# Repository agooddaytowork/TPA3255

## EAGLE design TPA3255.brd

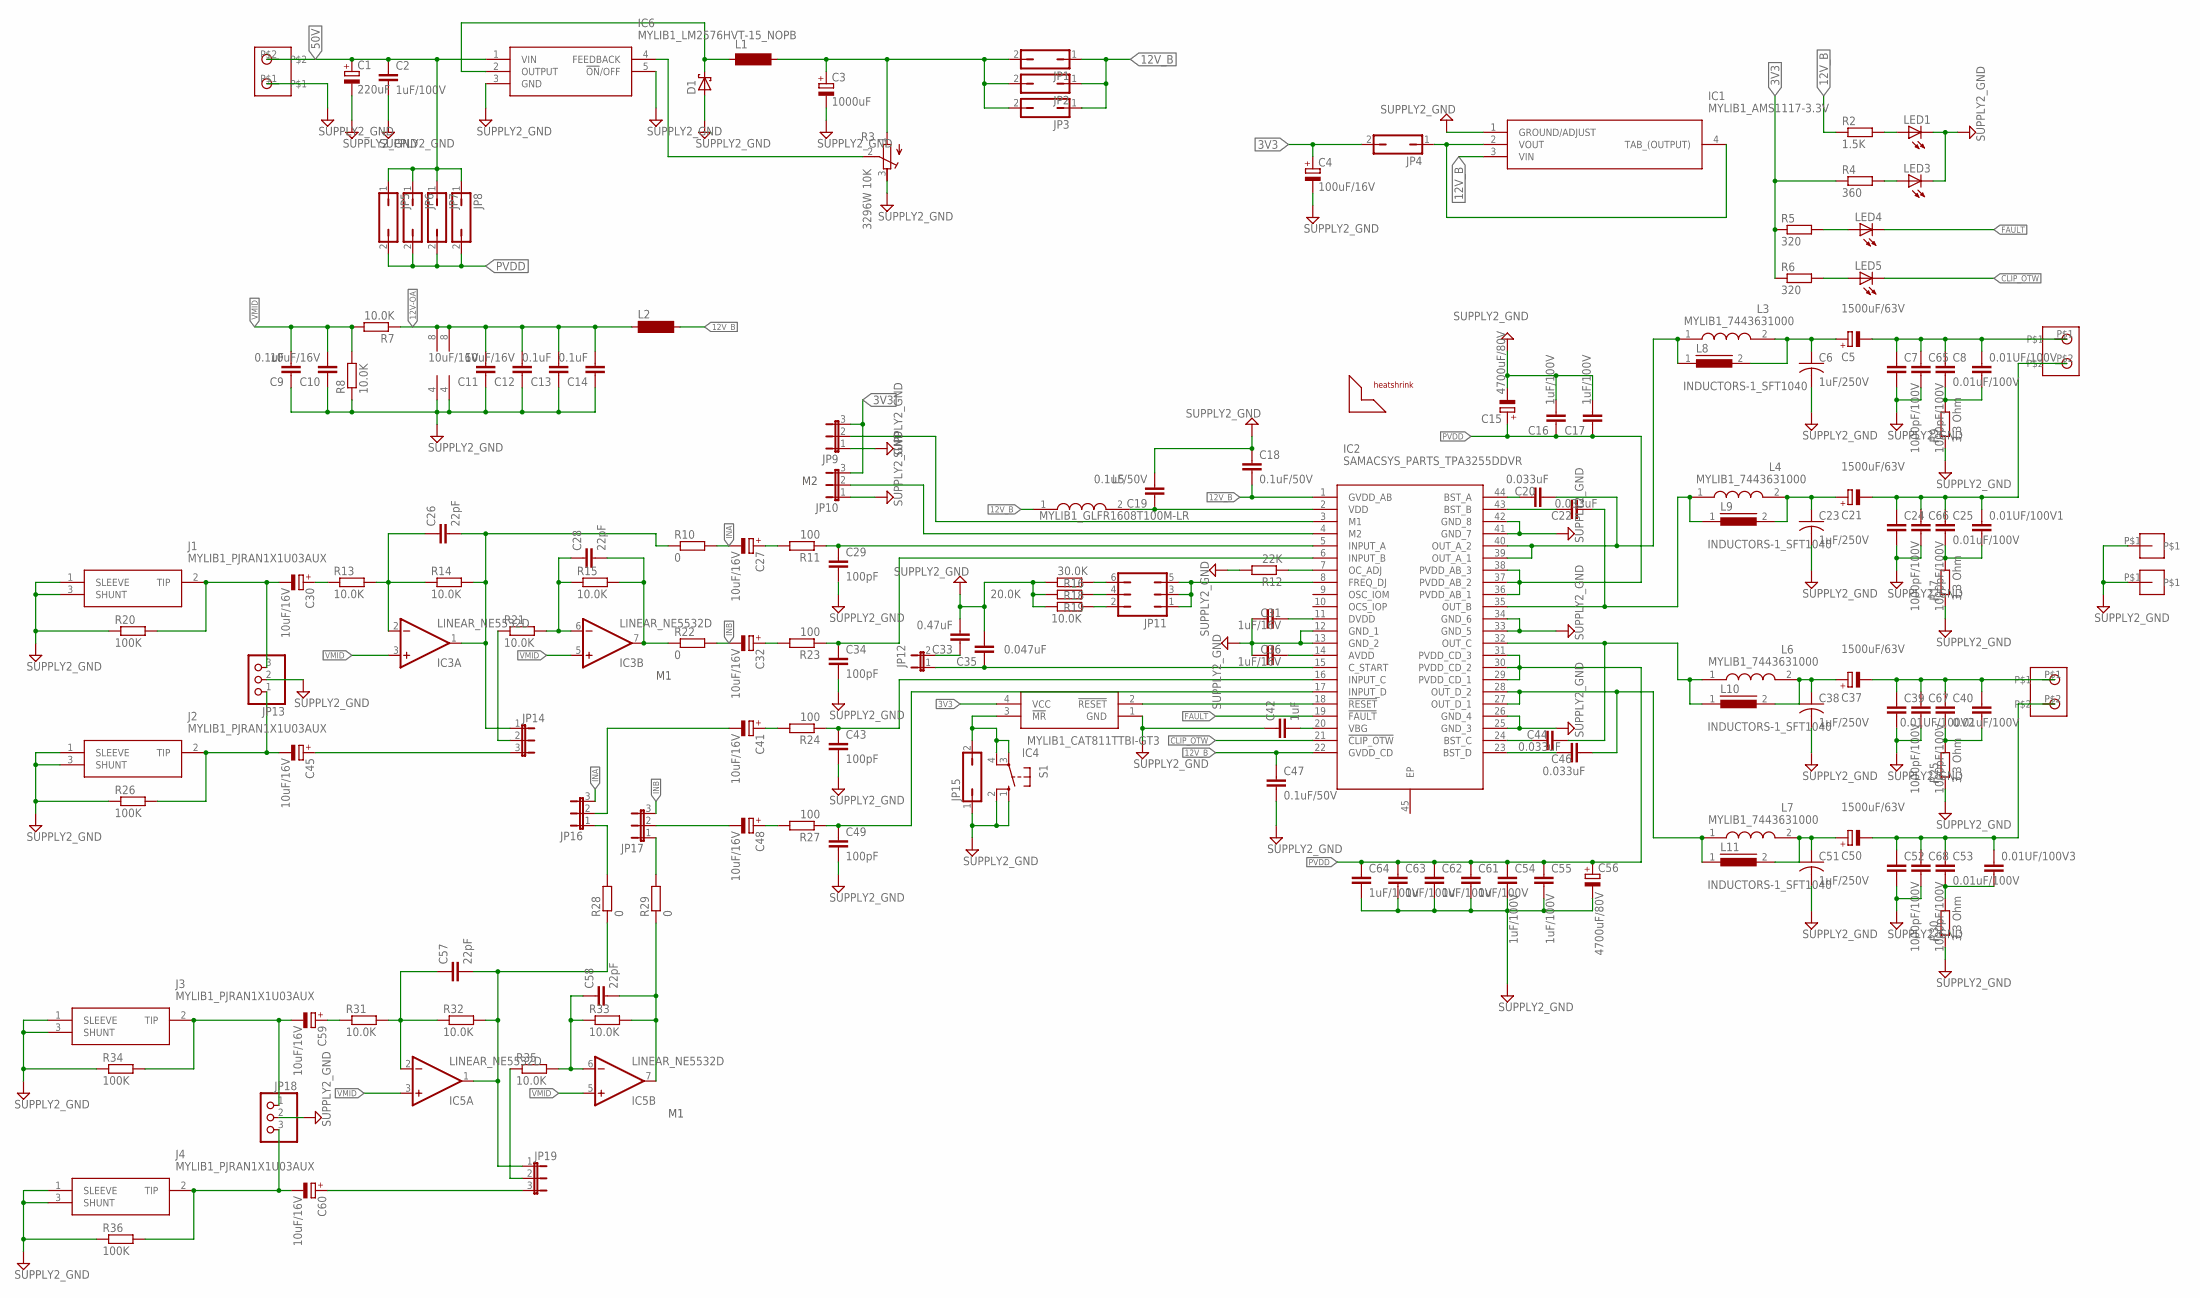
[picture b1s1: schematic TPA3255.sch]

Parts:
0.01UF/100V, 0.01UF/100V1, 0.01UF/100V2, 0.01UF/100V3: RCL_C-EU102-054X133; RCL_C102-054X133
C1: 220uF; RCL_E7,5-18
C2, C16, C17, C54, C55: 1uF/100V; RCL_C150-054X183
C3: 1000uF; RCL_E5-10,5
C4: 100uF/16V; RESISTOR_PANASONIC_B:1
C5, C21, C37, C50: 1500uF/63V; RCL_EB22,5D
C6, C23, C38, C51: 1uF/250V; RCL_C225-108X268
C7, C24, C39, C52: 1000pF/100V; RCL_C1206
C8, C25, C40, C53: 0.01uF/100V; RCL_C0603
C9, C13, C14: 0.1uF; RCL_C0805
C10, C11, C12: 10uF/16V; RCL_C0805
C15, C56: 4700uF/80V; RCL_EB35D
C18, C19, C47: 0.1uF/50V; RCL_C0603
C20, C22, C44, C46: 0.033uF; RCL_C0603K
C26, C28, C57, C58: 22pF; RCL_C0805
C27, C30, C32, C41, C45, C48, C59, C60: 10uF/16V; RCL_PANASONIC_B
C29, C34, C43, C49: 100pF; RCL_C0805
C31, C36: 1uF/16V; RCL_C0603
C33: 0.47uF; RCL_C0603
C35: 0.047uF; RCL_C0805
C42: 1uF; RESISTOR_C0603:1
C61, C62, C63, C64: 1uF/100V; RCL_C1206
C65, C66, C67, C68: 1000pF/100V; RCL_C050-025X075
D1: DIODE_SCHOTTKY-DIODESMD; DIODE_SMB
H1: 28x28mm; MYLIB1_HEATSHRINK-28X28MM
IC1: MYLIB1_AMS1117-3.3V; MYLIB1_SOT229P700X180-4N
IC2: SAMACSYS_PARTS_TPA3255DDVR; SAMACSYS_PARTS_SOP64P810X120-45N
IC3, IC5: LINEAR_NE5532D; LINEAR_SO08
IC4: MYLIB1_CAT811TTBI-GT3; MYLIB1_4-PIN-SOT-143(BI-SUFFIX-CASE-5
IC6: MYLIB1_LM2576HVT-15_NOPB; MYLIB1_LM2576HVT15NOPB
J1, J2, J3, J4: MYLIB1_PJRAN1X1U03AUX
JP1, JP2, JP3, JP4, JP5, JP6, JP7, JP8, JP15: JUMPER_JP1Q; JUMPER_JP1
JP9, JP10, JP14, JP16, JP17, JP19: JUMPER_JP2E; JUMPER_JP2
JP11: JUMPER_JP3Q
JP12: JUMPER_JP1E; JUMPER_JP1
JP13, JP18: PINHEAD_PINHD-1X3; PINHEAD_1X03
L1, L2: INDUCTOR-NEOSID_BS11
L3, L4, L6, L7: MYLIB1_7443631000; MYLIB1_WE-HCF_201322
L5: MYLIB1_GLFR1608T100M-LR; MYLIB1_INDC1608X100N
L8, L9, L10, L11: INDUCTORS-1_SFT1040
LED1, LED3, LED4, LED5: LED_LEDCHIP-LED0805; LED_CHIP-LED0805
R2: 1.5K; RCL_M0805
R3: 3296W 10K; RCL_RTRIM3296W
R4: 360; RCL_M0805
R5, R6: 320; RCL_M0805
R7, R8, R13, R14, R15, R21, R31, R32, R33, R35: 10.0K; RESISTOR_M0805:1
R9, R17, R25, R30: 3.3 Ohm; RESISTOR_R0805:1
R10, R22, R28, R29: 0; RESISTOR_M0805:1
R11, R23, R24, R27: 100; RCL_M0805
R12: 22K; RCL_M0805
R16: 30.0K; RCL_R0805
R18: 20.0K; RESISTOR_R0603:1
R19: 10.0K; RCL_R0805
R20, R26, R34, R36: 100K; RESISTOR_M0805:1
S1: SWITCH-OMRON_10-XX; SWITCH-OMRON_B3F-10XX
T1, T2, T4: MYLIB1_5MM-2PIN-TERMINAL; MYLIB1_3MM-2PIN-TERMINAL
U$1, U$2: MYLIB1_5MM-1PIN-TERMINAL

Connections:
3V3: C4.+, IC4.4 (VCC), JP4.2, JP9.3, JP10.3, R4.1, R5.1, R6.1
12V: C3.+, JP1.2, JP2.2, JP3.2, L1.2, R3.1 (A)
12V-OA: C11.2, C12.2, C13.2, C14.2, IC3.8 (V+), IC5.8 (V+), L2.1, R7.1
12V_B: C18.2, C47.1, IC1.3 (VIN), IC2.1 (GVDD_AB), IC2.22 (GVDD_CD), JP1.1, JP2.1, JP3.1, L2.2, L5.1, R2.1
50V: C1.+, C2.1, IC6.1 (VIN), JP5.1, JP6.1, JP7.1, JP8.1, T1.P$2
CLIP_OTW: IC2.21 (!CLIP_OTW), LED5.C
FAULT: IC2.19 (!FAULT), LED4.C
GND: C1.-, C2.2, C3.-, C4.-, C6.2, C7.2, C9.1, C10.1, C11.1, C12.1, C13.1, C14.1, C15.-, C16.2, C17.2, C18.1, C19.2, C23.2, C24.2, C29.2, C31.1, C33.2, C34.2, C35.2, C36.1, C38.2, C39.2, C42.1, C43.2, C47.2, C49.2, C51.2, C52.2, C54.2, C55.2, C56.-, C61.2, C62.2, C63.2, C64.2, C65.2, C66.2, C67.2, C68.2, D1.A, IC1.1 (GROUND/ADJUST), IC2.12 (GND_1), IC2.13 (GND_2), IC2.25 (GND_3), IC2.26 (GND_4), IC2.33 (GND_5), IC2.34 (GND_6), IC2.41 (GND_7), IC2.42 (GND_8), IC3.4 (V-), IC4.1 (GND), IC5.4 (V-), IC6.3 (GND), IC6.5 (!ON!/OFF), J1.1 (SLEEVE), J1.3 (SHUNT), J2.1 (SLEEVE), J2.3 (SHUNT), J3.1 (SLEEVE), J3.3 (SHUNT), J4.1 (SLEEVE), J4.3 (SHUNT), JP9.1, JP10.1, JP13.2, JP15.1, JP18.2, LED1.C, LED3.C, R3.3 (E), R8.1, R9.1, R12.2, R16.1, R17.1, R18.1, R19.1, R20.1, R25.1, R26.1, R30.1, R34.1, R36.1, S1.1 (S), S1.2 (S1), T1.P$1, U$1.P$1, U$2.P$1
INA: C27.-, JP16.3, R10.2
INB: C32.-, JP17.3, R22.2
unnamed: C34.1, IC2.6 (INPUT_B), R23.1
unnamed: C43.1, IC2.16 (INPUT_C), R24.1
unnamed: C49.1, IC2.17 (INPUT_D), R27.1
unnamed: IC2.3 (M1), JP9.2
unnamed: C29.1, IC2.5 (INPUT_A), R11.1
unnamed: IC2.4 (M2), JP10.2
unnamed: C35.1, IC2.15 (C_START), JP12.1
unnamed: IC2.7 (OC_ADJ), R12.1
unnamed: C33.1, JP12.2
unnamed: IC4.3 (!MR), JP15.2, S1.3, S1.4 (P1)
unnamed: LED4.A, R5.2
unnamed: LED5.A, R6.2
unnamed: C42.2, IC2.20 (VBG)
unnamed: C44.1, IC2.24 (BST_C)
unnamed: C46.1, IC2.23 (BST_D)
unnamed: C22.1, IC2.43 (BST_B)
unnamed: IC2.18 (!RESET), IC4.2 (!RESET)
unnamed: C20.1, IC2.44 (BST_A)
unnamed: 0.01UF/100V.2, C8.2, R9.2
unnamed: C5.+, C6.1, L3.2, L8.2
unnamed: 0.01UF/100V.1, C5.-, C7.1, C8.1, C65.1, T2.P$1
unnamed: C20.2, IC2.39 (OUT_A_1), IC2.40 (OUT_A_2), L3.1, L8.1
unnamed: 0.01UF/100V1.2, C25.2, R17.2
unnamed: C21.+, C23.1, L4.2, L9.2
unnamed: 0.01UF/100V1.1, C21.-, C24.1, C25.1, C66.1, T2.P$2
unnamed: C22.2, IC2.35 (OUT_B), L4.1, L9.1
unnamed: 0.01UF/100V2.1, C40.2, R25.2
unnamed: C37.+, C38.1, L6.2, L10.2
unnamed: 0.01UF/100V2.2, C37.-, C39.1, C40.1, C67.1, T4.P$1
unnamed: JP11.6, R16.2
unnamed: 0.01UF/100V3.2, C53.2, R30.2
unnamed: C50.+, C51.1, L7.2, L11.2
unnamed: 0.01UF/100V3.1, C50.-, C52.1, C53.1, C68.1, T4.P$2
unnamed: C44.2, IC2.32 (OUT_C), L6.1, L10.1
unnamed: C46.2, IC2.27 (OUT_D_1), IC2.28 (OUT_D_2), L7.1, L11.1
unnamed: IC2.8 (FREQ_DJ), JP11.1, JP11.3, JP11.5
unnamed: JP11.4, R18.2
unnamed: JP11.2, R19.2
unnamed: C36.2, IC2.14 (AVDD)
unnamed: C31.2, IC2.11 (DVDD)
unnamed: C30.+, R13.1
unnamed: LED3.A, R4.2
unnamed: C19.1, IC2.2 (VDD), L5.2
unnamed: IC1.2 (VOUT), IC1.4 (TAB_(OUTPUT)), JP4.1
unnamed: D1.C, IC6.2 (OUTPUT), L1.1
unnamed: IC6.4 (FEEDBACK), R3.2 (S)
unnamed: LED1.A, R2.2
unnamed: C45.+, JP14.3
unnamed: C26.1, IC3.2 (-IN), R13.2, R14.1
unnamed: C26.2, IC3.1 (OUT), JP14.1, R10.1, R14.2
unnamed: JP14.2, R21.1
unnamed: C28.1, IC3.6 (-IN), R15.1, R21.2
unnamed: C28.2, IC3.7 (OUT), R15.2, R22.1
unnamed: JP17.1, R29.2
unnamed: C27.+, R11.2
unnamed: C48.-, JP17.2
unnamed: C32.+, R23.2
unnamed: C59.+, R31.1
unnamed: C57.1, IC5.2 (-IN), R31.2, R32.1
unnamed: C57.2, IC5.1 (OUT), JP19.1, R28.1, R32.2
unnamed: C60.+, JP19.3
unnamed: JP19.2, R35.1
unnamed: C58.1, IC5.6 (-IN), R33.1, R35.2
unnamed: C58.2, IC5.7 (OUT), R29.1, R33.2
unnamed: JP16.1, R28.2
unnamed: C41.-, JP16.2
unnamed: C48.+, R27.2
unnamed: C41.+, R24.2
unnamed: C30.-, J1.2 (TIP), JP13.3, R20.2
unnamed: C45.-, J2.2 (TIP), JP13.1, R26.2
unnamed: C59.-, J3.2 (TIP), JP18.1, R34.2
unnamed: C60.-, J4.2 (TIP), JP18.3, R36.2
PVDD: C15.+, C16.1, C17.1, C54.1, C55.1, C56.+, C61.1, C62.1, C63.1, C64.1, IC2.29 (PVDD_CD_1), IC2.30 (PVDD_CD_2), IC2.31 (PVDD_CD_3), IC2.36 (PVDD_AB_1), IC2.37 (PVDD_AB_2), IC2.38 (PVDD_AB_3), JP5.2, JP6.2, JP7.2, JP8.2
VMID: C9.2, C10.2, IC3.3 (+IN), IC3.5 (+IN), IC5.3 (+IN), IC5.5 (+IN), R7.2, R8.2

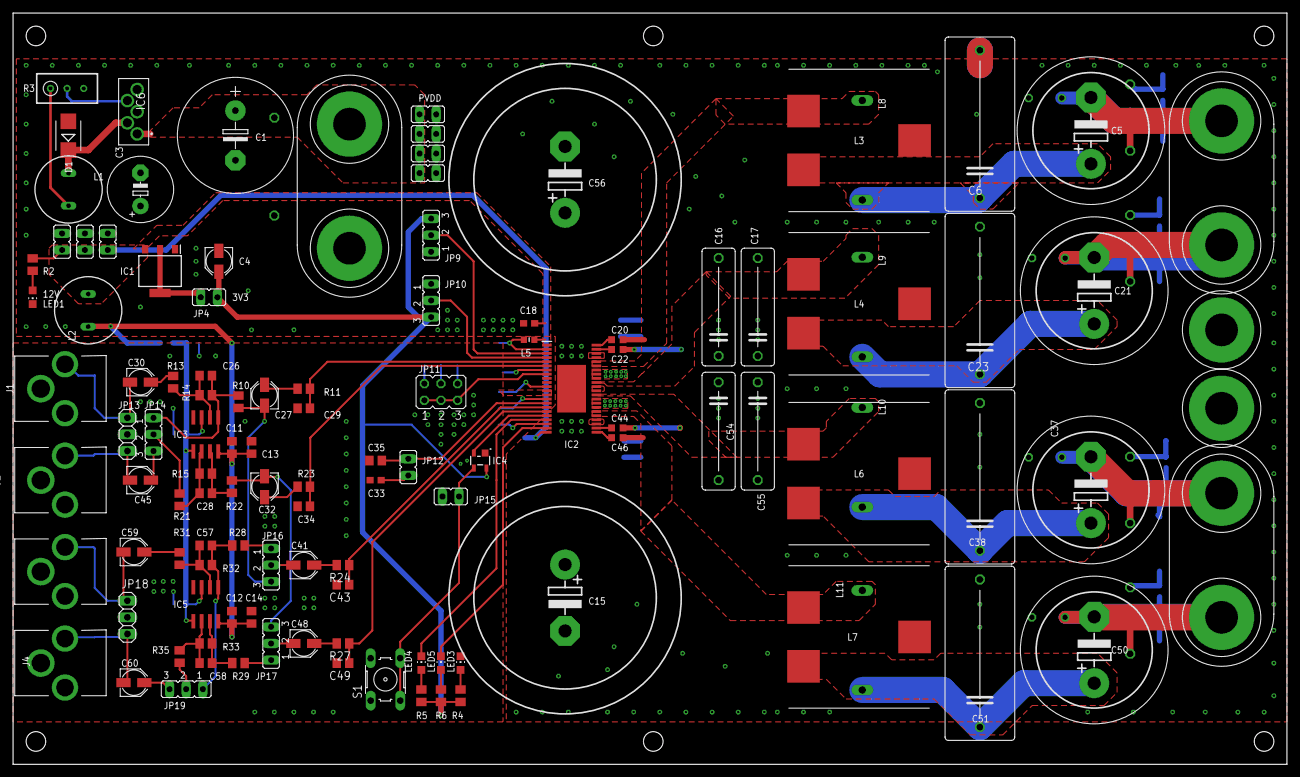
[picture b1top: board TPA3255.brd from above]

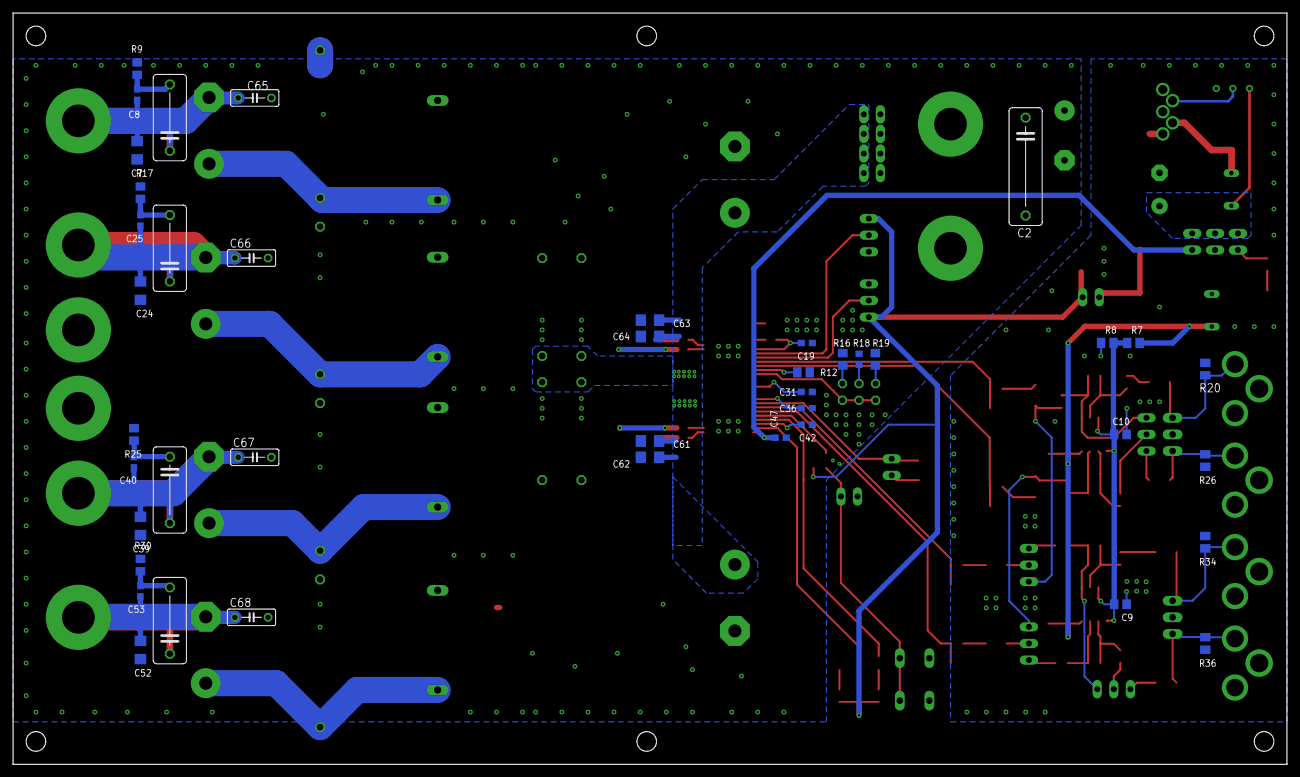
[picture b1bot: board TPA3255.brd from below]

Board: 2 copper layers, 195.0 x 115.0 mm, 159 parts (42 on the bottom side), 84 nets.

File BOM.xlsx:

Qty | Value | Device | Package | Parts | Description | MANUFACTURER_NAME | MANUFACTURER_PART_NUMBER | MOUSER_PART_NUMBER
1 |  | JP1E | JP1 | JP12 | JUMPER | https://icdayroi.com/header-1x40-2-54mm-17mm-male
9 |  | JP1Q | JP1 | JP1, JP2, JP3, JP4, JP5, JP6, JP7, JP8, JP15 | JUMPER | https://icdayroi.com/header-1x40-2-54mm-17mm-male
6 |  | JP2E | JP2 | JP9, JP10, JP14, JP16, JP17, JP19 | JUMPER | https://icdayroi.com/header-1x40-2-54mm-17mm-male
1 |  | JP3Q | JP3Q | JP11 | JUMPER | https://icdayroi.com/header-1x40-2-54mm-17mm-male
4 |  | LEDCHIP-LED0805 | CHIP-LED0805 | LED1, LED3, LED4, LED5 | LED | https://icdayroi.com/led-green-0805
1 |  | MS75 | MS75 | L2 / 0912 | INDUCTOR | https://icdayroi.com/cuon-cam-10uh-0912
2 |  | PINHD-1X3 | 1X03 | JP13, JP18 | PIN HEADER | https://icdayroi.com/header-1x40-2-54mm-17mm-male
1 |  | SCHOTTKY-DIODESMD | SMB | D1 | Schottky Diode | https://icdayroi.com/smbj12ca
4 | 0 | R-EU_M0805 | M0805 | R10, R22, R28, R29 | RESISTOR, European symbol | https://icdayroi.com/dien-tro-0-ohm-0805-5-goi-50-con
4 | 0.01uF/100V | C-EUC0603/through hole | C0603 | C8, C25, C40, C53 | CAPACITOR, European symbol | https://icdayroi.com/tu-10nf-400v-400v103j | VJ0603Y103KXBAC31X | 77-V0603Y103KXBAC31X
4 | 0.033uF | C-EUC0603K | C0603K | C20, C22, C44, C46 | CAPACITOR, European symbol | https://icdayroi.com/tu-dien-33nf-50v-0603 | 885012206068 | 710-885012206068
1 | 0.047uF | C-EUC0805 | C0805 | C35 | CAPACITOR, European symbol | https://icdayroi.com/tu-dien-47nf-50v-0603
3 | 0.1uF | C-EUC0805 | C0805 | C9, C13, C14 | CAPACITOR, European symbol | https://icdayroi.com/tu-dien-100nf-50v-0603
3 | 0.1uF/50V | C-EUC0603 | C0603 | C18, C19, C47 | CAPACITOR, European symbol | https://icdayroi.com/tu-dien-100nf-50v-0603 | CC0603MRY5V9BB104 | 603-C0603MRY5V9BB104
1 | 0.47uF | C-EUC0805 - 0603 | C0805 | C33 | CAPACITOR, European symbol | https://icdayroi.com/tu-dien-470nf-50v-0603
1 | 1.5K | R-EU_M0805 | M0805 | R2 | RESISTOR, European symbol | https://icdayroi.com/dien-tro-1-5k-0805-1-goi-50-con
10 | 10.0K | R-EU_M0805 | M0805 | R7, R8, R13, R14, R15, R21, R31, R32, R33, R35 | RESISTOR, European symbol | https://icdayroi.com/dien-tro-10k-0805-1-goi-50-con
1 | 10.0K | R-EU_R0805 | R0805 | R19 | RESISTOR, European symbol | https://icdayroi.com/dien-tro-10k-0805-1-goi-50-con
4 | 100 | R-EU_M0805 | M0805 | R11, R23, R24, R27 | RESISTOR, European symbol | https://icdayroi.com/dien-tro-100-ohm-0805-1-goi-50-con
4 | 1000pF/100V | C-EUC1206 | C1206 | C7, C24, C39, C52 | CAPACITOR, European symbol | https://icdayroi.com/tu-1nf-100v-100v102j | 885012208106 | 710-885012208106
1 | 1000uF | CPOL-EUE5-10.5 | E5-10,5 | C3 | POLARIZED CAPACITOR, European symbol | https://icdayroi.com/tu-hoa-1000uf100v
4 | 100K | R-EU_M0805 | M0805 | R20, R26, R34, R36 | RESISTOR, European symbol | https://icdayroi.com/dien-tro-100k-0805-1-goi-50-con
4 | 100pF | C-EUC0805 | C0805 | C29, C34, C43, C49 | CAPACITOR, European symbol | https://icdayroi.com/tu-dien-100pf-50v-0805
1 | 100uF/16V | CPOL-EUC - size B8 | PANASONIC_C | C4 | POLARIZED CAPACITOR, European symbol | https://icdayroi.com/aluminum-capacitor-smd-100uf35v
3 | 10uF/16V | C-EUC0805 | C0805 | C10, C11, C12 | CAPACITOR, European symbol | https://icdayroi.com/tu-dien-10uf-50v-0805
8 | 10uF/16V | CPOL-EUB | PANASONIC_B | C27, C30, C32, C41, C45, C48, C59, C60 | POLARIZED CAPACITOR, European symbol | https://icdayroi.com/aluminum-capacitor-smd-10uf25v
4 | 1500uF/63V | CPOL-EUE7.5-18 | E7,5-18 | C5, C21, C37, C50 | POLARIZED CAPACITOR, European symbol | https://icdayroi.com/tu-hoa-1000uf100v | 860020781027 | 710-860020781027
1 | 1uF/50V | C-EUC0805 / 0603 | C0805 | C42 | CAPACITOR, European symbol | https://icdayroi.com/tu-dien-1uf-50v-0603 | CC0805KFX7R9BB105 | 603-CC0805KFX7R9BB10
5 | 1uF/100V | C-EUC1206 /through hole | C1206 | C2, C16, C17, C54, C55 | CAPACITOR, European symbol | https://icdayroi.com/tu-1uf-250v-250v105j | GRJ31CR72A105KE11L | 81-GRJ31CR72A105KE1L
2 | 1uF/16V | C-EUC0603 | C0603 | C31, C36 | CAPACITOR, European symbol | https://icdayroi.com/tu-dien-1uf-50v-0603
4 | 1uF/250V | C-EU150-091X182 | C150-091X182 | C6, C23, C38, C51 | CAPACITOR, European symbol | https://icdayroi.com/tu-vang-1uf-275v-22-5mm | MKS4-1/250/10P15 | 505-MKS4-1/250/10P15
1 | 20.0K | R-EU_R0805/0603 | R0805 | R18 | RESISTOR, European symbol | https://thegioiic.com/products/dien-tro-20k-ohm-0603-1
1 | 220uF | CPOL-EUE7.5-18 | E7,5-18 | C1 | POLARIZED CAPACITOR, European symbol | https://icdayroi.com/tu-hoa-220uf50v
1 | 22K | R-EU_M0805 | M0805 | R12 | RESISTOR, European symbol | https://icdayroi.com/dien-tro-22k-0805-1-goi-50-con
4 | 22pF | C-EUC0805 | C0805 | C26, C28, C57, C58 | CAPACITOR, European symbol | https://icdayroi.com/tu-dien-22pf-50v-0805
1 | 28x28mm | HEATSHRINK-28X28MM | HEATSHRINK-28X28MM | H1 |  | https://thegioiic.com/products/nhom-tan-nhiet-28x28x15-dan-cpu
4 | 3.3 Ohm | R-EU_R0603 / 0805 | R0603 | R9, R17, R25, R30 | RESISTOR, European symbol | https://icdayroi.com/dien-tro-3-3-ohm-0805-1-goi-50-con
1 | 30.0K | R-EU_R0805 | R0805 | R16 | RESISTOR, European symbol | https://thegioiic.com/products/dien-tro-30k-ohm-0805-1
2 | 320 | R-EU_M0805 | M0805 | R5, R6 | RESISTOR, European symbol | https://icdayroi.com/dien-tro-390-ohm-0805-1-goi-50-con
1 | 3296W 10K | R-TRIMM3296W | RTRIM3296W | R3 | Trimm resistor | https://icdayroi.com/bien-tro-tinh-chinh-10k-3296w-103
1 | 360 | R-EU_M0805 | M0805 | R4 | RESISTOR, European symbol | https://icdayroi.com/dien-tro-390-ohm-0805-1-goi-50-con
2 | 4700uF/80V | CPOL-EUE10-35 | EB35D | C15, C56 | POLARIZED CAPACITOR, European symbol | https://icdayroi.com/tu-hoa-3300uf100v | LLS1K472MELC | 647-LLS1K472MELC
4 | 5MM-2PIN-TERMINAL | 5MM-2PIN-TERMINAL | 3MM-2PIN-TERMINAL | T1, T2, T3, T4
4 | 7443631000 | 7443631000 | WE-HCF_201322 | L3, L4, L6, L7 | Wurth WE-HCF Series Shielded Wire-wound SMD Inductor with a Ferrite Core, 10 H 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 | Wurth Elektronik | 7443631000 | 710-7443631000
1 | 82114R | 82114R | 82114R | L1 | INDUCTOR | https://icdayroi.com/cuon-cam-100uh-0912 | https://icdayroi.com/cuon-cam-100uh-0912
1 | AMS1117-3.3V | AMS1117-3.3V | SOT229P700X180-4N | IC1 | 1A LOW DROPOUT VOLTAGE REGULATOR, SOT-223 | https://icdayroi.com/ams1117-3-3v | ams1117-3.3v
1 | CAT811TTBI-GT3 | CAT811TTBI-GT3 | 4-PIN-SOT-143(BI-SUFFIX-CASE-5 | IC4 | uP PSU Supervisory IC Vth=3.075V SOT-143 ON Semiconductor CAT811TTBI-GT3, Volta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 | ON Semiconductor | CAT811TTBI-GT3 | 698-CAT811TTBI-GT3
1 | GLFR1608T100M-LR | GLFR1608T100M-LR / 10UH CD74R | INDC1608X100N | L5 | TDK - GLFR1608T100M-LR - POWER LINE IND, 10UH,400MA,20% | https://icdayroi.com/cuon-cam-10uh-cd74r | MLZ1608E100MT | 810-MLZ1608E100MT
1 | LM2576HVS-ADJ/NOPB | LM2576HVS-ADJ/NOPB | REG_LM2576HVS-ADJ/NOPB | U1 | IC REG BUCK ADJ 3A DDPAK | https://thegioiic.com/products/lm2576hvt-12v
2 | NE5532D | NE5532D | SO08 | IC3, IC5 | AUDIO AMPLIFIER | https://icdayroi.com/ne5532dr
4 | PJRAN1X1U03AUX | PJRAN1X1U03AUX | PJRAN1X1U03AUX | J1, J2, J3, J4 | RCA Phono Connectors 1 POS RA PHONO JACK | Switchcraft | PJRAN1X1U03AUX | 502-PJRAN1X1U03AUX
4 | SFT1040 | SFT1040 | SFT1040 | L8, L9, L10, L11 | INDUCTOR | https://thegioiic.com/products/cuon-cam-10uh-5026-3a-18x13-xuyen-lo
1 | TPA3255DDVR | TPA3255DDVR | SOP64P810X120-45N | IC2 | 315W Stereo / 600W Mono PurePath Ultra-HD, Analog-In Class-D Amplifier | Texas Instruments | TPA3255DDVR
